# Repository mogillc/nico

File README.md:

# nico
The nico hexapod hardware and software files.

http://svn.mogi.io:8080/api/api/

To purchase 3D printed models please visit our shapeways store:
https://www.shapeways.com/shops/mogi

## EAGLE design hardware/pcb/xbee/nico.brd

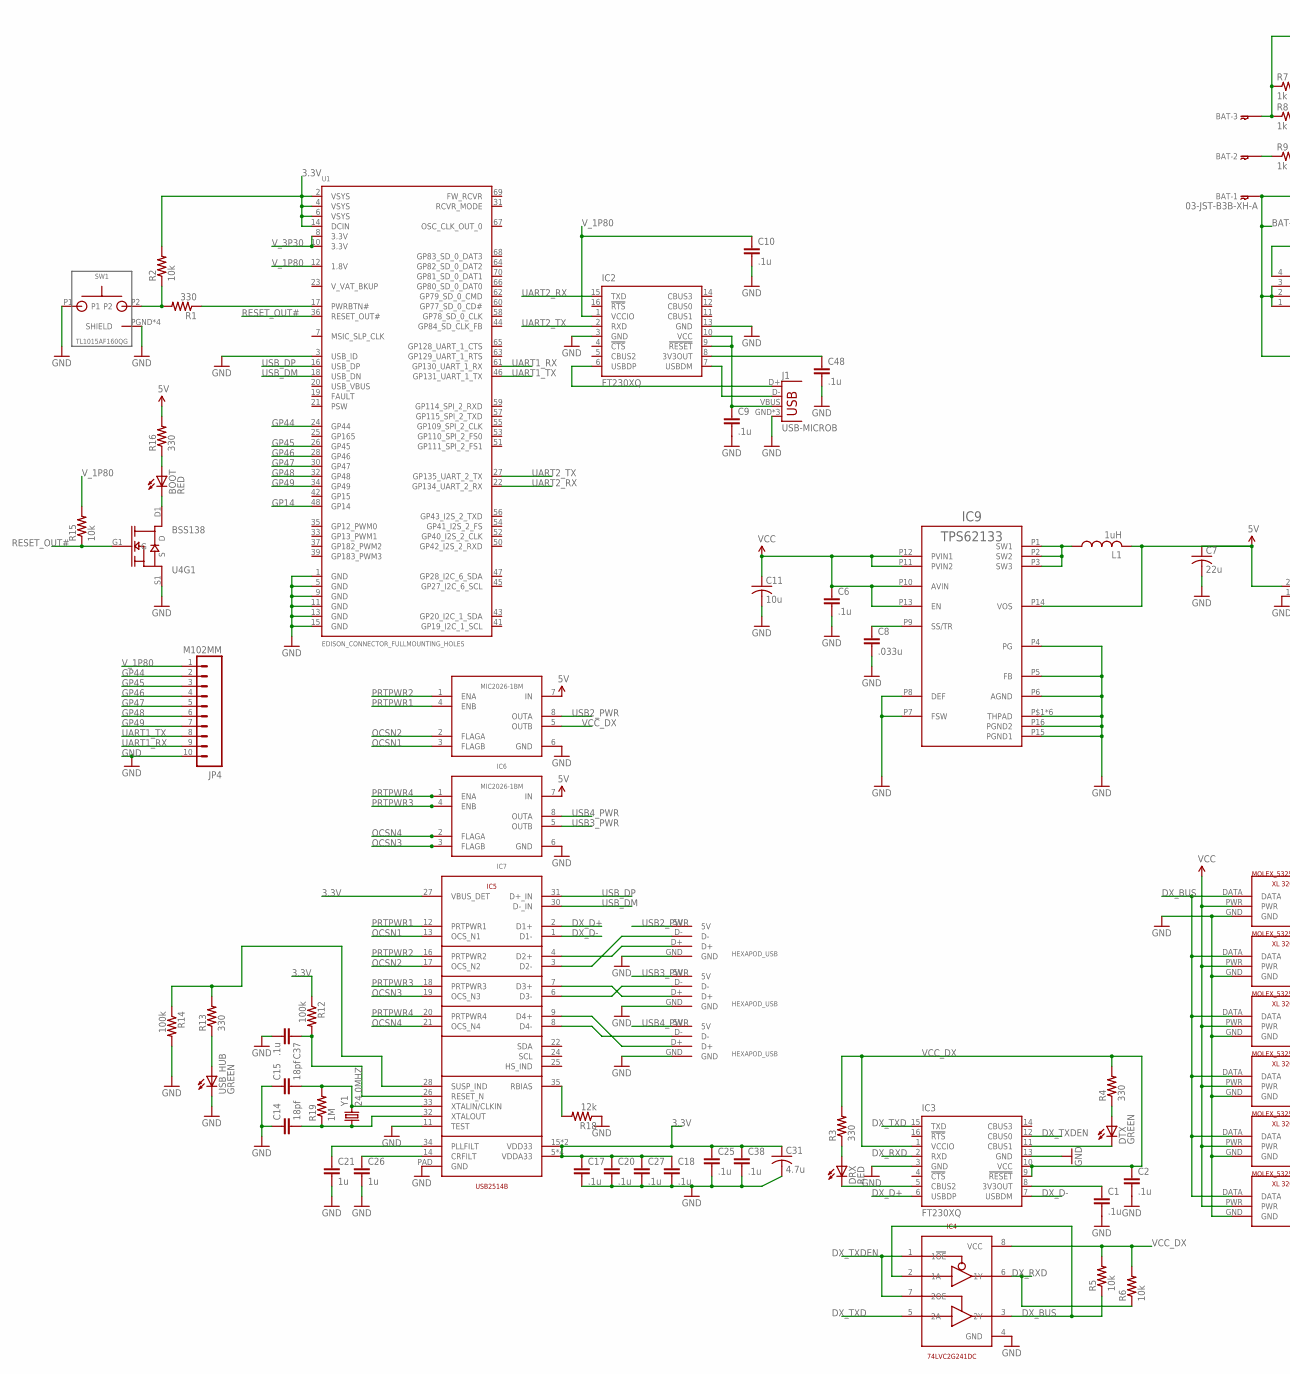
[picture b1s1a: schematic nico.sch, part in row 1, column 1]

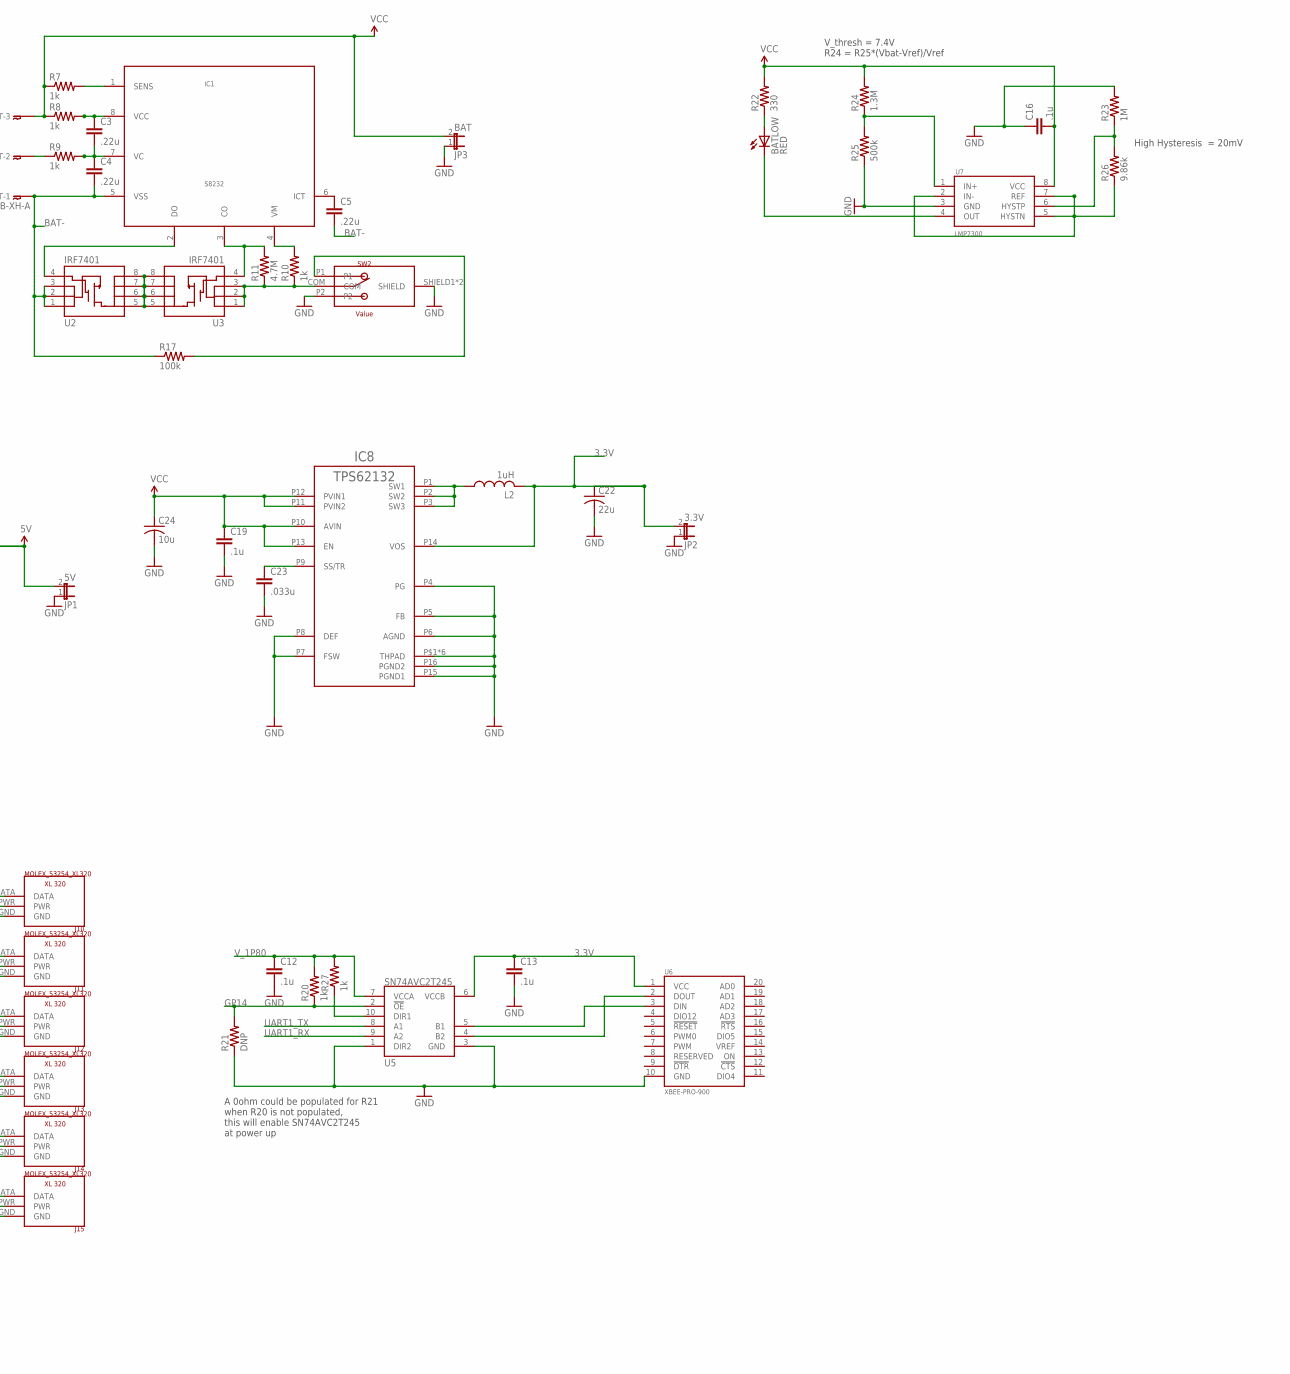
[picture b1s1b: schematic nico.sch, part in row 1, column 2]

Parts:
BAT: 03-JST-B3B-XH-A; B3B-XH
BATLOW: RED; LED-0603
BOOT: RED; LED-0603
C1, C2, C6, C9, C10, C12, C13, C16, C17, C18, C19, C20, C25, C27, C37, C38, C48: .1u; C0402
C3, C4, C5: .22u; C0402
C7, C22: 22u; C0603
C8, C23: .033u; C0402
C11, C24: 10u; C0805
C14, C15: 18pf; C0402
C21, C26: 1u; C0402
C31: 4.7u; C0603
DRX: RED; LED-0603
DTX: GREEN; LED-0603
IC1: S8232; TSSOP8
IC2, IC3: FT230XQ; QFN16
IC4: 74LVC2G241DC; VSSOP
IC5: USB2514B; 36-QFN
IC6, IC7: MIC2026-1BM; 8-SOIC
IC8: TPS62132; VQFN-16
IC9: TPS62133; VQFN-16
J1: USB-MICROB
J2, J3, J4: HEXAPOD_USB; MOLEX_53254_4POS
J10, J11, J12, J13, J14, J15: MOLEX_53254_XL320; MOLES_53254_XL320
JP1: 5V; 1X02
JP2: 3.3V; 1X02
JP3: BAT; 1X02
JP4: M102MM; 1X10-2MM
L1, L2: 1uH; L2825P
R1, R3, R4, R13, R16, R22: 330; R0402
R2, R5, R6, R15: 10k; R0402
R7, R8, R9, R10, R20, R27: 1k; C0402
R11: 4.7M; C0402
R12, R14, R17: 100k; C0402
R18: 12k; C0402
R19, R23: 1M; C0402
R21: DNP; C0402
R24: 1.3M; C0402
R25: 500k; C0402
R26: 9.86k; C0402
SW1: TL1015AF160QG
SW2: TOGGLE_SWITCH_ET01MD1AGE
U1: EDISON_CONNECTOR_FULLMOUNTING_HOLES; EDISON_DAUGHTER
U2, U3: IRF7401; SO08
U4: BSS138; SOT363
U5: SN74AVC2T245; RSW-UQFN-10
U6: XBEE-PRO-900; XBEE-PRO-OEM
U7: LMP7300; 8-SOIC
USB_HUB: GREEN; LED-0603
Y1: 24.0MHZ; CRYSTAL-SMD-5X3

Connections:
3.3V: C13.1, C17.1, C18.1, C20.1, C22.1, C25.1, C27.1, C31.1, C38.1, IC5.5 (VDDA33), IC5.10 (VDDA33), IC5.15 (VDD33), IC5.23 (VDD33), IC5.27 (VBUS_DET), IC5.29 (VDDA33), IC5.36 (VDDA33), IC8.P14 (VOS), JP2.2, L2.2, R2.2, R12.1, U1.2 (VSYS), U1.4 (VSYS), U1.6 (VSYS), U1.14 (DCIN), U5.6 (VCCB), U6.1 (VCC)
5V: C7.1, IC6.7 (IN), IC7.7 (IN), IC9.P14 (VOS), JP1.2, L1.2, R16.2
BAT-: BAT.P$1, C4.2, C5.2, IC1.5 (VSS), R17.1, U2.1 (S), U2.2 (S), U2.3 (S)
DX_BUS: IC4.2 (1A), IC4.3 (2Y), J10.DATA, J11.DATA, J12.DATA, J13.DATA, J14.DATA, J15.DATA, R5.1
DX_D+: IC3.6 (USBDP), IC5.2 (D1+)
DX_D-: IC3.7 (USBDM), IC5.1 (D1-)
DX_RXD: IC3.2 (RXD), IC4.6 (1Y), R6.1
DX_TXD: IC3.15 (TXD), IC4.5 (2A)
DX_TXDEN: IC3.12 (CBUS0), IC4.1 (1!OE), IC4.7 (2OE)
GND: C1.2, C2.2, C6.2, C7.2, C8.2, C9.2, C10.2, C11.2, C12.2, C13.2, C14.1, C15.1, C16.1, C17.2, C18.2, C19.2, C20.2, C21.2, C22.2, C23.2, C24.2, C25.2, C26.2, C27.2, C31.2, C37.2, C38.2, C48.2, IC2.3 (GND), IC2.13 (GND), IC3.3 (GND), IC3.13 (GND), IC4.4 (GND), IC5.11 (TEST), IC5.PAD (GND), IC6.6 (GND), IC7.6 (GND), IC8.P4 (PG), IC8.P5 (FB), IC8.P6 (AGND), IC8.P7 (FSW), IC8.P8 (DEF), IC8.P15 (PGND1), IC8.P16 (PGND2), IC8.P$1 (THPAD), IC8.P$2 (THPAD), IC8.P$3 (THPAD), IC8.P$4 (THPAD), IC8.P$5 (THPAD), IC8.P$6 (THPAD), IC9.P4 (PG), IC9.P5 (FB), IC9.P6 (AGND), IC9.P7 (FSW), IC9.P8 (DEF), IC9.P15 (PGND1), IC9.P16 (PGND2), IC9.P$1 (THPAD), IC9.P$2 (THPAD), IC9.P$3 (THPAD), IC9.P$4 (THPAD), IC9.P$5 (THPAD), IC9.P$6 (THPAD), J1.GND, J1.MT1 (GND), J1.MT2 (GND), J2.GND, J3.GND, J4.GND, J10.GND, J11.GND, J12.GND, J13.GND, J14.GND, J15.GND, JP1.1, JP2.1, JP3.1, JP4.10, R14.2, R18.1, R21.1, R23.2, R25.1, SW1.P1, SW1.PGND (SHIELD), SW1.PGND2 (SHIELD), SW1.PGND3 (SHIELD), SW1.PGND4 (SHIELD), SW2.P2, SW2.SHIELD1 (SHIELD), SW2.SHIELD2 (SHIELD), U1.1 (GND), U1.3 (USB_ID), U1.5 (GND), U1.9 (GND), U1.11 (GND), U1.13 (GND), U1.15 (GND), U4.S1 (S), U5.1 (DIR2), U5.3 (GND), U6.10 (GND), U7.3 (GND), USB_HUB.C
GP14: R20.1, R21.2, U1.48 (GP14), U5.2 (!OE)
GP44: JP4.2, U1.24 (GP44)
GP45: JP4.3, U1.26 (GP45)
GP46: JP4.4, U1.28 (GP46)
GP47: JP4.5, U1.30 (GP47)
GP48: JP4.6, U1.32 (GP48)
GP49: JP4.7, U1.34 (GP49)
unnamed: R1.2, R2.1, SW1.P2
unnamed: DRX.C, IC3.5 (CBUS2)
unnamed: C1.1, IC3.8 (3V3OUT)
unnamed: IC2.6 (USBDP), J1.D+
unnamed: C15.2, IC5.33 (XTALIN/CLKIN), R19.2, Y1.3 (2)
unnamed: C14.2, IC5.32 (XTALOUT), R19.1, Y1.1
unnamed: IC5.7 (D3+), J3.D+
unnamed: C3.2, C4.1, IC1.7 (VC), R9.2
unnamed: C3.1, IC1.8 (VCC), R8.2
unnamed: R1.1, U1.17 (PWRBTN#)
unnamed: C8.1, IC9.P9 (SS/TR)
unnamed: R13.1, USB_HUB.A
unnamed: DTX.A, R4.1
unnamed: C21.1, IC5.34 (PLLFILT)
unnamed: C26.1, IC5.14 (CRFILT)
unnamed: DTX.C, IC3.11 (CBUS1)
unnamed: IC8.P1 (SW1), IC8.P2 (SW2), IC8.P3 (SW3), L2.1
unnamed: IC2.7 (USBDM), J1.D-
unnamed: C37.1, IC5.26 (RESET_N), R12.2
unnamed: C9.1, IC2.9 (!RESET), IC2.10 (VCC), J1.VBUS
unnamed: DRX.A, R3.1
unnamed: C23.1, IC8.P9 (SS/TR)
unnamed: IC5.9 (D4+), J4.D+
unnamed: IC5.28 (SUSP_IND), R13.2, R14.1
unnamed: C48.1, IC2.8 (3V3OUT)
unnamed: IC5.35 (RBIAS), R18.2
unnamed: IC5.8 (D4-), J4.D-
unnamed: C5.1, IC1.6 (ICT)
unnamed: IC1.1 (SENS), R7.2
unnamed: BAT.P$2, R9.1
unnamed: IC5.6 (D3-), J3.D-
unnamed: IC1.4 (VM), R10.2
unnamed: R10.1, R11.1, SW2.COM, U3.1 (S), U3.2 (S), U3.3 (S)
unnamed: BOOT.C, U4.D1 (D)
unnamed: U2.5 (D), U2.6 (D), U2.7 (D), U2.8 (D), U3.5 (D), U3.6 (D), U3.7 (D), U3.8 (D)
unnamed: BOOT.A, R16.1
unnamed: IC1.2 (DO), U2.4 (G)
unnamed: IC1.3 (CO), R11.2, U3.4 (G)
unnamed: IC5.3 (D2-), J2.D-
unnamed: IC5.4 (D2+), J2.D+
unnamed: IC9.P1 (SW1), IC9.P2 (SW2), IC9.P3 (SW3), L1.1
unnamed: R17.2, SW2.P1
unnamed: BATLOW.C, U7.4 (OUT)
unnamed: BATLOW.A, R22.1
unnamed: R26.1, U7.2 (IN-), U7.5 (HYSTN), U7.7 (REF)
unnamed: R23.1, R26.2, U7.6 (HYSTP)
unnamed: R24.1, R25.2, U7.1 (IN+)
unnamed: R27.1, U5.10 (DIR1)
unnamed: U5.5 (B1), U6.3 (DIN)
unnamed: U5.4 (B2), U6.2 (DOUT)
OCSN1: IC5.13 (OCS_N1), IC6.3 (FLAGB)
OCSN2: IC5.17 (OCS_N2), IC6.2 (FLAGA)
OCSN3: IC5.19 (OCS_N3), IC7.3 (FLAGB)
OCSN4: IC5.21 (OCS_N4), IC7.2 (FLAGA)
PRTPWR1: IC5.12 (PRTPWR1), IC6.4 (ENB)
PRTPWR2: IC5.16 (PRTPWR2), IC6.1 (ENA)
PRTPWR3: IC5.18 (PRTPWR3), IC7.4 (ENB)
PRTPWR4: IC5.20 (PRTPWR4), IC7.1 (ENA)
RESET_OUT#: R15.1, U1.36 (RESET_OUT#), U4.G1 (G)
UART1_RX: JP4.9, U1.61 (GP130_UART_1_RX), U5.9 (A2)
UART1_TX: JP4.8, U1.46 (GP131_UART_1_TX), U5.8 (A1)
UART2_RX: IC2.15 (TXD), U1.22 (GP134_UART_2_RX)
UART2_TX: IC2.2 (RXD), U1.27 (GP135_UART_2_TX)
USB2_PWR: IC6.8 (OUTA), J2.5V
USB3_PWR: IC7.5 (OUTB), J3.5V
USB4_PWR: IC7.8 (OUTA), J4.5V
USB_DM: IC5.30 (D-_IN), U1.18 (USB_DN)
USB_DP: IC5.31 (D+_IN), U1.16 (USB_DP)
VCC: BAT.P$3, C6.1, C11.1, C16.2, C19.1, C24.1, IC8.P10 (AVIN), IC8.P11 (PVIN2), IC8.P12 (PVIN1), IC8.P13 (EN), IC9.P10 (AVIN), IC9.P11 (PVIN2), IC9.P12 (PVIN1), IC9.P13 (EN), J10.PWR, J11.PWR, J12.PWR, J13.PWR, J14.PWR, J15.PWR, JP3.2, R7.1, R8.1, R22.2, R24.2, U7.8 (VCC)
VCC_DX: C2.1, IC3.1 (VCCIO), IC3.9 (!RESET), IC3.10 (VCC), IC4.8 (VCC), IC6.5 (OUTB), R3.2, R4.2, R5.2, R6.2
V_1P80: C10.1, C12.1, IC2.1 (VCCIO), JP4.1, R15.2, R20.2, R27.2, U1.12 (1.8V), U5.7 (VCCA)
V_3P30: U1.8 (3.3V), U1.10 (3.3V)

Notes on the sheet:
A 0ohm could be populated for R21 when R20 is not populated, this will enable SN74AVC2T245 at power up
V_thresh = 7.4V R24 = R25*(Vbat-Vref)/Vref
High Hysteresis = 20mV

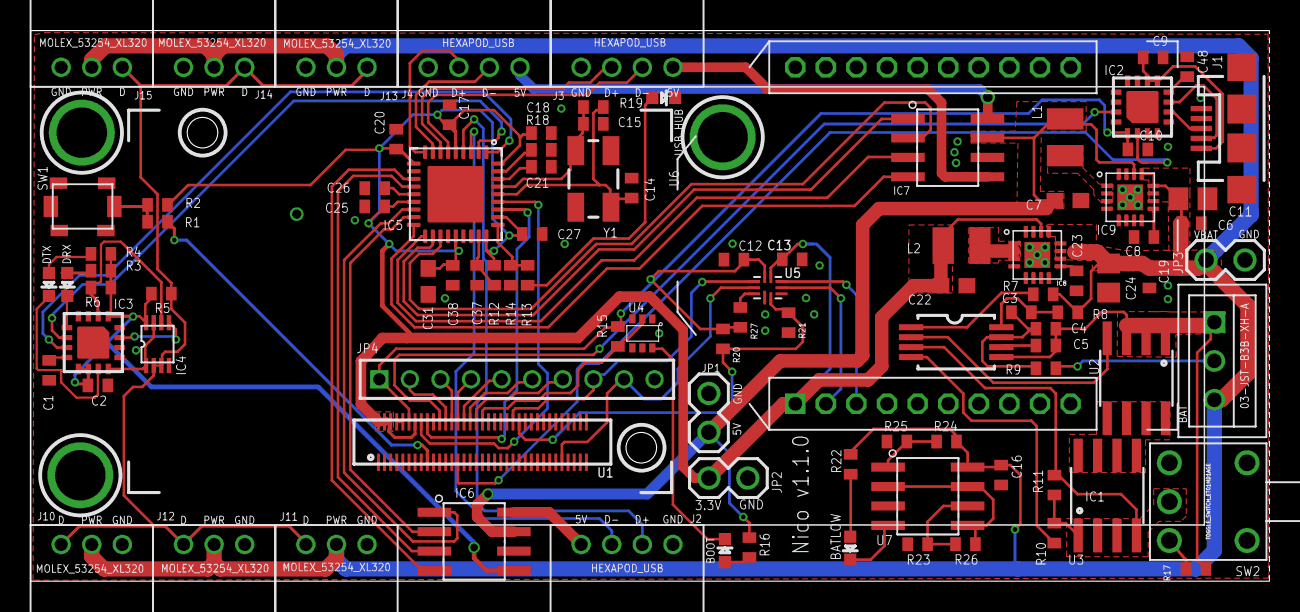
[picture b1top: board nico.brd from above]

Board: 2 copper layers, 81.0 x 36.0 mm, 99 parts (0 on the bottom side), 89 nets.

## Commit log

2015-06-25 first commit with PCB design
2015-06-25 removed the hidden ds_store file
2015-12-02 added xbee version
2016-02-10 Adding libmogi sources and examples.
2016-02-12 Further decoupling of jsoncpp and assimp
2016-02-22 aadded API links
2016-02-22 adding API links
2016-02-25 Updates to verbose level of dynamixel interface. Support for iOS and Android being implemented.
2016-03-03 add .gitignore for intermediate folder like build
2016-03-03 when verbose is enabled, print the buffer in hex array format for readInterface and writeInterface
2016-03-03 add 20ms delay for yuneec servo firmware
2016-03-11 Fixed json vlaue creation bug. Also added improvements to mogisim
2016-08-25 Moved to LGPL
2016-09-05 Added shapewasy link
2016-10-25 Added STL files and instructions
2021-04-19 copied line caused compile error
2021-04-20 Fisxed threads linker issue
2022-05-10 Update deprecated cmake version

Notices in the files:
parts and their libraries:
SparkFun-Connectors: Licensing: Creative Commons ShareAlike 4.0 International - https://creativecommons.org/licenses/by-sa/4.0
